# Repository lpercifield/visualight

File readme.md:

###**Visualight Hardware and Firmware**
Server code is available from this repo

####**Release Candidate GREEN**

Current Firmware Version: 1.1 (RC GREEN) library
More information: [Visualight.org][1]

* Arduino Library can be found in Firmware > Visualight
* Wiki can be found [here][2]

------
	
####Features:
* Show color (version) of firmware when you do a reset
* Ability to enable/disable WiFly LEDs from Arduino (top-level)
* Special character support in SSIDs (now supports &^%$#()!@ in network name)

####Fixes:
* Easier to reset WiFi with button (processButton() added to reconnect loops
* Debug toggling from Arduino?

[1]:http://visualight.org
[2]:https://github.com/lpercifield/visualight/wiki
[3]:https://github.com/lpercifield/Visualight_Server

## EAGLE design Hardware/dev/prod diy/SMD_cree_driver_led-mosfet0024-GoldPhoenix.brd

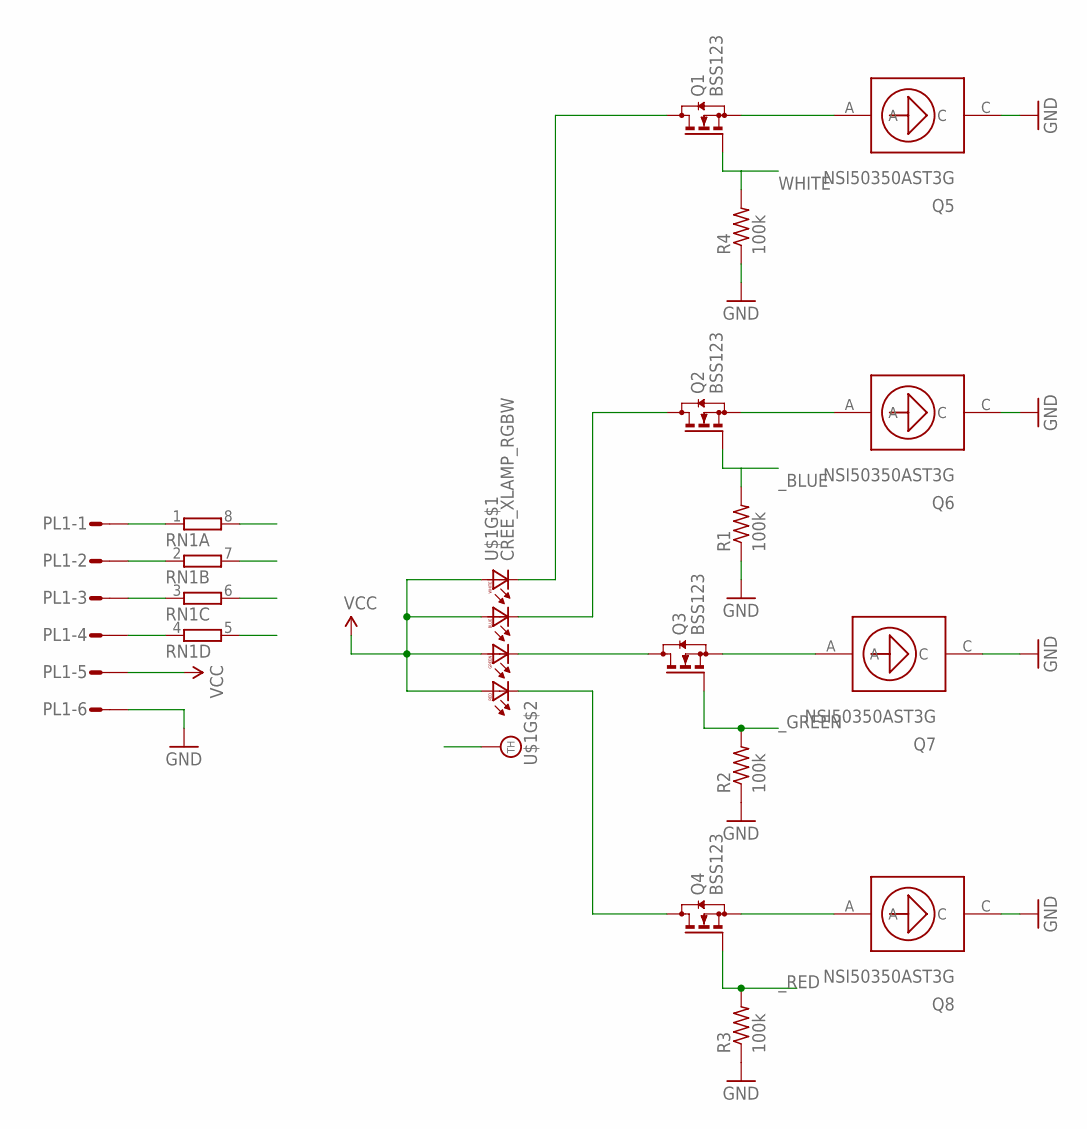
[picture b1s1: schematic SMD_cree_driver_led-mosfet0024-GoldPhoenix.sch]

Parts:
PL1: DF3-06R; DF3R-06
Q1, Q2, Q3, Q4: BSS123; SOT23
Q5, Q6, Q7, Q8: NSI50350AST3G; SMC-2
R1, R2, R3, R4: 100k; R0402
RN1: 4R-N0603-ARC; 0603-ARC
U$1: CREE_XLAMP_RGBW; CREE_XLAMP_XML

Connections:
BLUE_DRIVER: Q2.3 (D), U$1.6 (BC)
BLUE_PWM_IN: PL1.3, RN1.3 (1)
GND: PL1.6, Q5.C, Q6.C, Q7.C, Q8.C, R1.1, R2.1, R3.1, R4.1
GREEN_DRIVER: Q3.3 (D), U$1.7 (GC)
GREEN_PWM_IN: PL1.4, RN1.4 (1)
unnamed: Q2.2 (S), Q6.A
unnamed: Q4.2 (S), Q8.A
unnamed: Q3.2 (S), Q7.A
unnamed: Q1.2 (S), Q5.A
RED_DRIVER: Q4.3 (D), U$1.8 (RC)
RED_PWM_IN: PL1.2, RN1.2 (1)
THERM: U$1.P$1 (TH)
VCC: PL1.5, U$1.1 (RA), U$1.2 (GA), U$1.3 (BA), U$1.4 (WA)
WHITE: Q1.1 (G), R4.2, RN1.8 (2)
WHITE_DRIVER: Q1.3 (D), U$1.5 (WC)
WHITE_PWM_IN: PL1.1, RN1.1
_BLUE: Q2.1 (G), R1.2, RN1.6 (2)
_GREEN: Q3.1 (G), R2.2, RN1.5 (2)
_RED: Q4.1 (G), R3.2, RN1.7 (2)

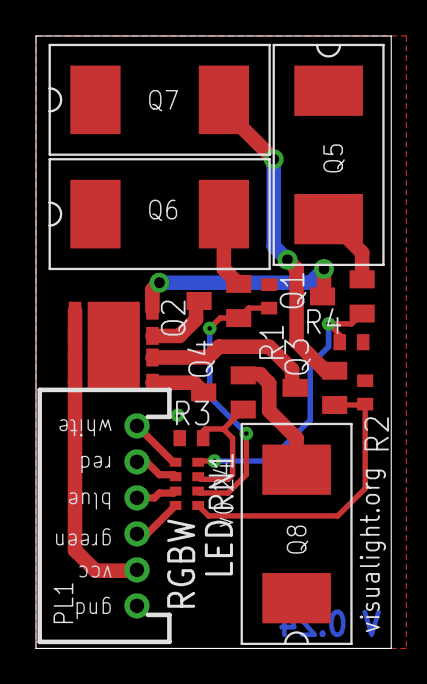
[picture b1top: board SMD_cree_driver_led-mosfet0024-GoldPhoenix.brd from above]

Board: 2 copper layers, 19.7 x 34.0 mm, 15 parts (0 on the bottom side), 18 nets.

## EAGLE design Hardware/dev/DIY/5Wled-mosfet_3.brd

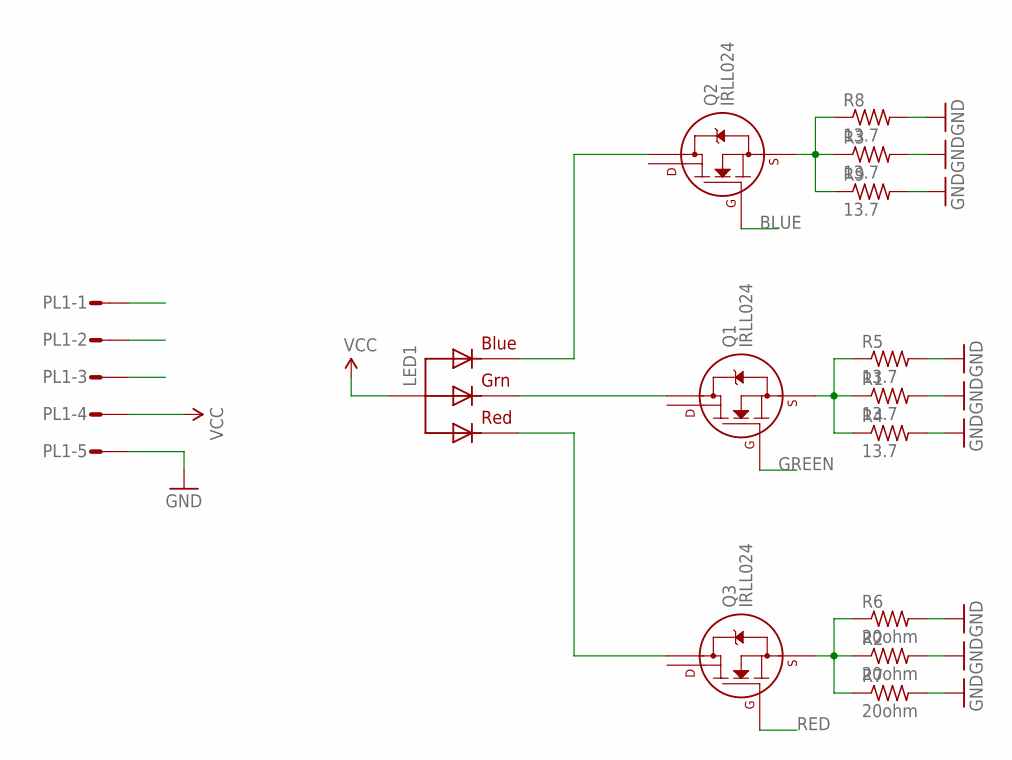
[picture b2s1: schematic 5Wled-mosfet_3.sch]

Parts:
LED1: RGBLED_CA4.5MM; 5WRGBLED
PL1: DF3-05R; DF3R-05
Q1, Q2, Q3: IRLL024; SOT-223
R1, R3, R4, R5, R8, R9: 13.7; R1210
R2, R6, R7: 20ohm; R1210

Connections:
BLUE: PL1.3, Q2.1 (G)
GND: PL1.5, R1.2, R2.2, R3.2, R4.2, R5.2, R6.2, R7.2, R8.2, R9.2
GREEN: PL1.1, Q1.1 (G)
unnamed: LED1.3 (GREEN), Q1.2 (D1)
unnamed: LED1.1 (BLUE), Q2.2 (D1)
unnamed: LED1.2 (RED), Q3.2 (D1)
unnamed: Q1.3 (S), R1.1, R4.1, R5.1
unnamed: Q3.3 (S), R2.1, R6.1, R7.1
unnamed: Q2.3 (S), R3.1, R8.1, R9.1
RED: PL1.2, Q3.1 (G)
VCC: LED1.4 (VCC), PL1.4

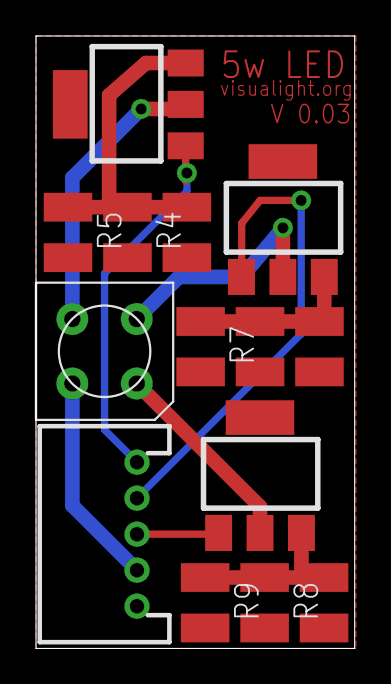
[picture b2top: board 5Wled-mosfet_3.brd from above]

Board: 2 copper layers, 17.7 x 34.0 mm, 14 parts (0 on the bottom side), 11 nets.

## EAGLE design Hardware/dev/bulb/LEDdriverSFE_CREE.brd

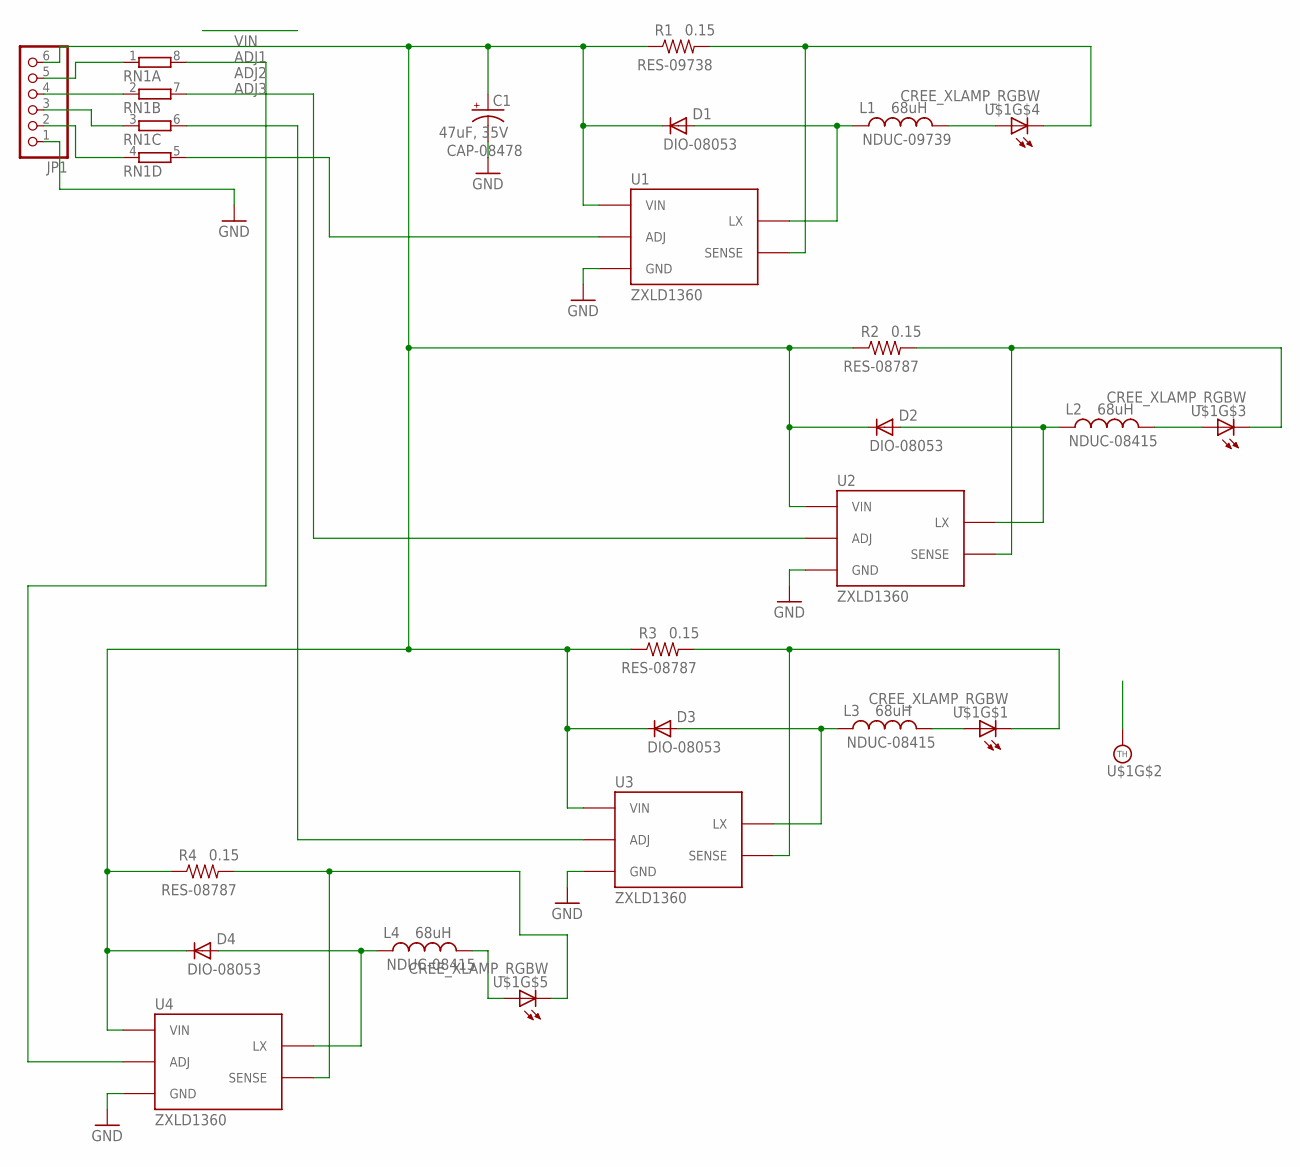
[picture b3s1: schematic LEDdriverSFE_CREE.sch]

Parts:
C1: 47uF, 35V; PANASONIC_D
D1, D2, D3, D4: MBRA140; SMA-DIODE
JP1: PINHD-1X6; 1X06
L1, L2, L3, L4: 68uH; CR75
R1, R2, R3, R4: 0.15; 0603-RES
RN1: 4R-NEXBV8V; EXBV8V
U1, U2, U3, U4: ZXLD1360; SOT23-5
U$1: CREE_XLAMP_RGBW; CREE_XLAMP_XML

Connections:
ADJ1: RN1.5 (2), U1.3 (ADJ)
ADJ2: RN1.7 (2), U2.3 (ADJ)
ADJ3: RN1.6 (2), U3.3 (ADJ)
GND: C1.-, JP1.1, U1.2 (GND), U2.2 (GND), U3.2 (GND), U4.2 (GND)
unnamed: L1.P$2 (2), U$1.3 (A)
unnamed: D2.A, L2.P$1 (1), U2.1 (LX)
unnamed: R2.2, U2.4 (SENSE), U$1.7 (C)
unnamed: D1.A, L1.P$1 (1), U1.1 (LX)
unnamed: R1.2, U1.4 (SENSE), U$1.6 (C)
unnamed: L2.P$2 (2), U$1.2 (A)
unnamed: D3.A, L3.P$1 (1), U3.1 (LX)
unnamed: R3.2, U3.4 (SENSE), U$1.8 (C)
unnamed: L3.P$2 (2), U$1.1 (A)
unnamed: D4.A, L4.P$1 (1), U4.1 (LX)
unnamed: R4.2, U4.4 (SENSE), U$1.5 (C)
unnamed: RN1.8 (2), U4.3 (ADJ)
unnamed: JP1.2, RN1.4 (1)
unnamed: JP1.5, RN1.1
unnamed: L4.P$2 (2), U$1.4 (A)
unnamed: JP1.4, RN1.2 (1)
unnamed: JP1.3, RN1.3 (1)
THERM: U$1.P$1 (TH)
VIN: C1.+, D1.C, D2.C, D3.C, D4.C, JP1.6, R1.1, R2.1, R3.1, R4.1, U1.5 (VIN), U2.5 (VIN), U3.5 (VIN), U4.5 (VIN)

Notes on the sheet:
NDUC-09739
RES-09738
CAP-08478
DIO-08053
NDUC-08415
RES-08787

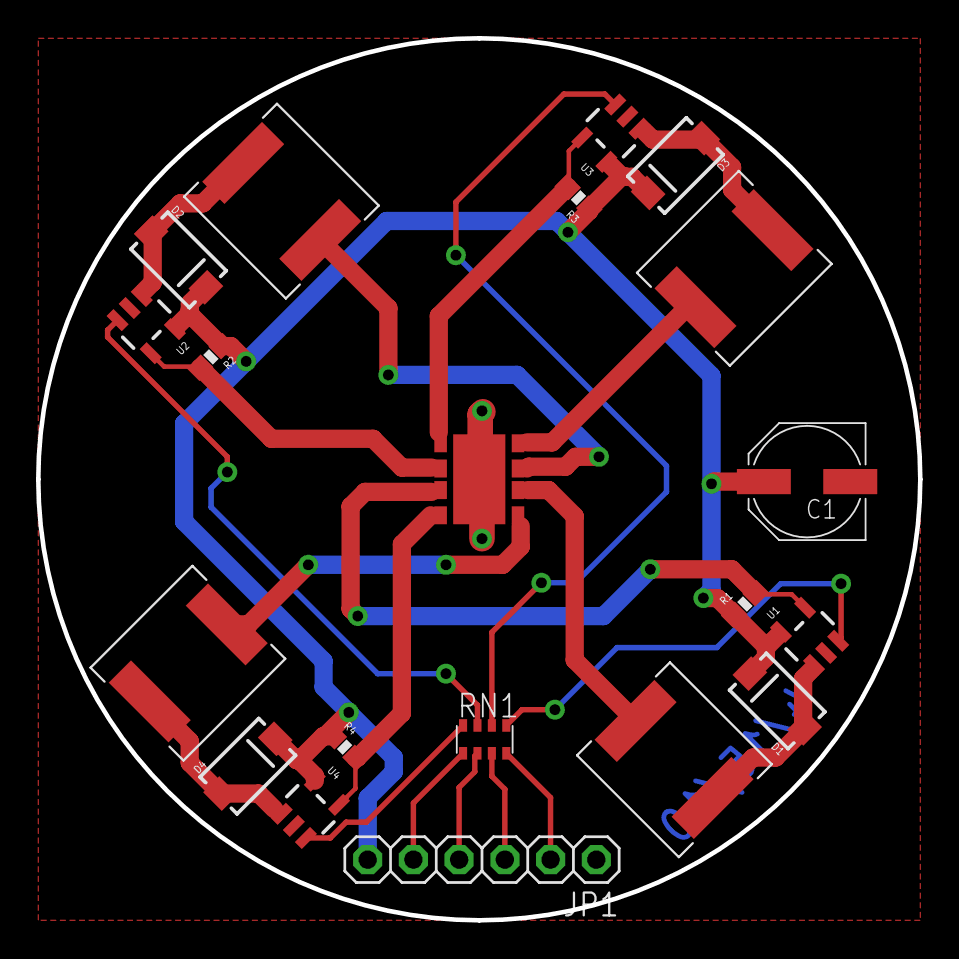
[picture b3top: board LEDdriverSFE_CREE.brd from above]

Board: 2 copper layers, 49.0 x 49.0 mm, 20 parts (0 on the bottom side), 22 nets.

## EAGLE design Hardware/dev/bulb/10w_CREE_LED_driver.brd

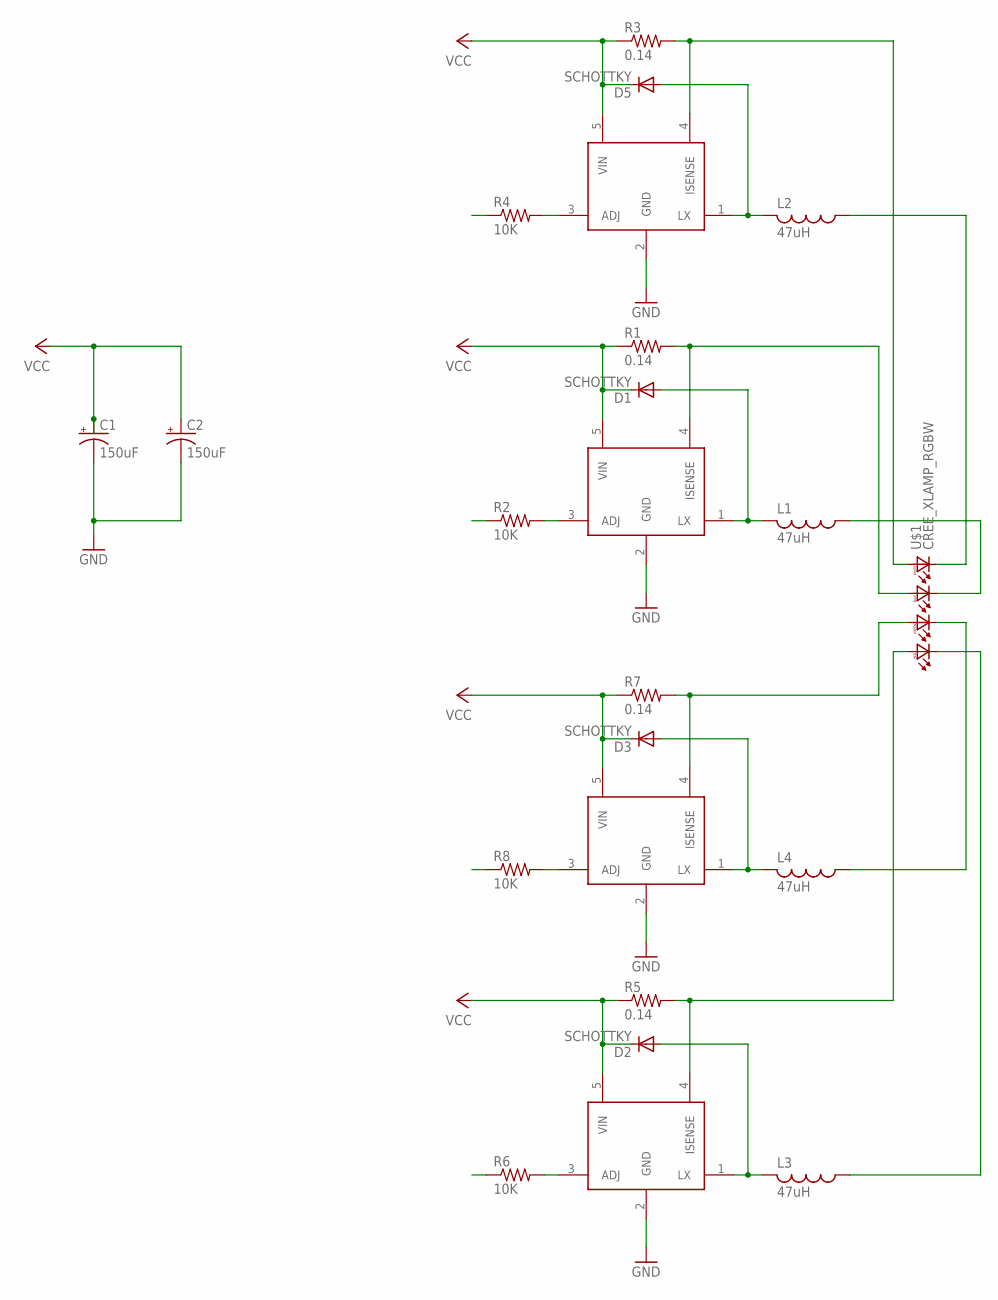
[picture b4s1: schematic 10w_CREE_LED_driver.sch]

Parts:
C1, C2: 150uF; 175TMP-0810
D1, D2, D3, D5: SCHOTTKY; DO214AC
L1, L2, L3, L4: 47uH; TDK6045
R1, R3, R5, R7: 0.14; R0805
R2, R4, R6, R8: 10K; R0603
U$1: CREE_XLAMP_RGBW; CREE_XLAMP_XML
U$2, U$3, U$4, U$6: ZLED7000-LEDDRIVER; SOT89-5

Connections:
GND: C1.-, C2.-, U$2.2 (GND), U$3.2 (GND), U$4.2 (GND), U$6.2 (GND)
unnamed: R2.2, U$2.3 (ADJ)
unnamed: R1.2, U$1.3 (BA), U$2.4 (ISENSE)
unnamed: L2.1, U$1.5 (WC)
unnamed: D1.A, L1.2, U$2.1 (LX)
unnamed: R3.2, U$1.4 (WA), U$6.4 (ISENSE)
unnamed: D5.A, L2.2, U$6.1 (LX)
unnamed: R4.2, U$6.3 (ADJ)
unnamed: R5.2, U$1.1 (RA), U$3.4 (ISENSE)
unnamed: D2.A, L3.2, U$3.1 (LX)
unnamed: R6.2, U$3.3 (ADJ)
unnamed: R7.2, U$1.2 (GA), U$4.4 (ISENSE)
unnamed: D3.A, L4.2, U$4.1 (LX)
unnamed: R8.2, U$4.3 (ADJ)
unnamed: L1.1, U$1.6 (BC)
unnamed: L4.1, U$1.7 (GC)
unnamed: L3.1, U$1.8 (RC)
VCC: C1.+, C2.+, D1.C, D2.C, D3.C, D5.C, R1.1, R3.1, R5.1, R7.1, U$2.5 (VIN), U$3.5 (VIN), U$4.5 (VIN), U$6.5 (VIN)

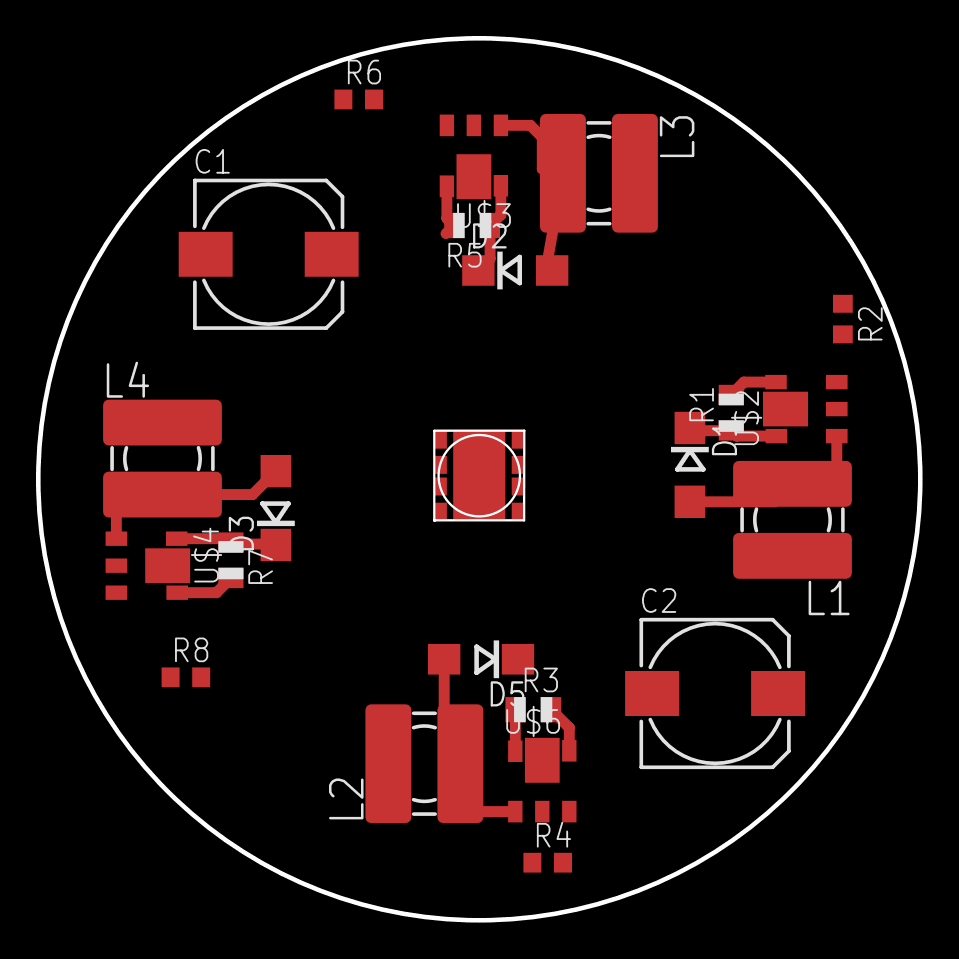
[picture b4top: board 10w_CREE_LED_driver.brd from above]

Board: 2 copper layers, 49.0 x 49.0 mm, 23 parts (0 on the bottom side), 18 nets.

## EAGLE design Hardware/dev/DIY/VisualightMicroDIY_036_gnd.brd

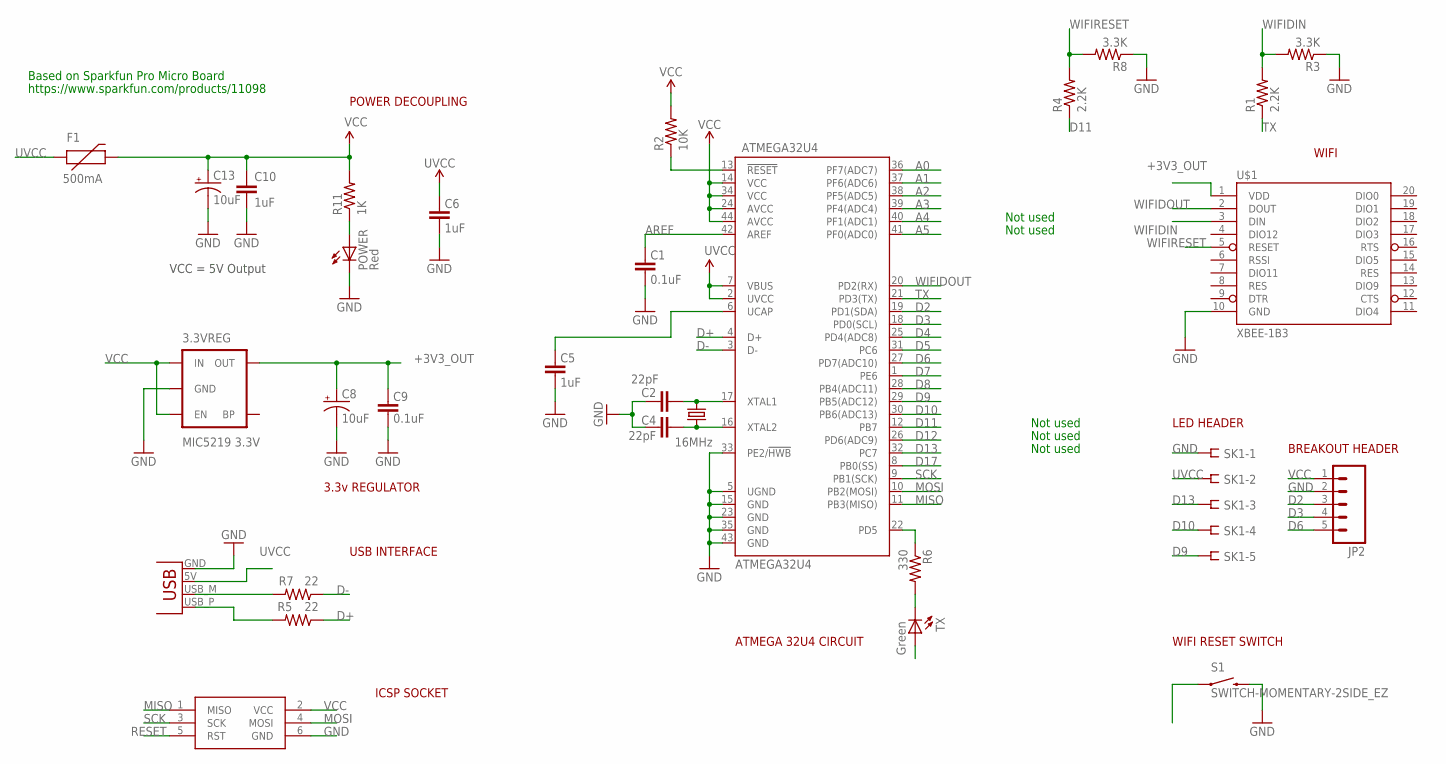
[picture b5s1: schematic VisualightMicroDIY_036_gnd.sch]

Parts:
3.3VREG: MIC5219 3.3V; SOT23-5
ATMEGA32U4: ATMEGA32U4; SPARKFUN-DIGITALIC_TQFP44
C1, C9: 0.1uF; 0402-CAP
C2, C4: 22pF; 0402-CAP
C5, C6, C10: 1uF; 0402-CAP
C8, C13: 10uF; EIA3216
F1: 500mA; PTC-1206
ISP1: AVRISP-6; AVRISP
JP2: M05PTH; 1X05
POWER: Red; LED-0603
R1, R4: 2.2K; 0402-RES
R2: 10K; 0402-RES
R3, R8: 3.3K; 0402-RES
R5, R7: 22; 0402-RES
R6: 330; 0402-RES
R11: 1K; 0402-RES
S1: SWITCH-MOMENTARY-2SIDE_EZ; TACTILE-PTH-SIDEEZ
SK1: DF3-05S; DF3S-05
TX: Green; LED-0603
U$1: XBEE-1B3; XBEE-SMD
X2: USBPCB; USB-A-PCB
Y1: 16MHz; CRYSTAL-SMD-5X3

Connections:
+3V3_OUT: 3.3VREG.5 (OUT), C8.A (+), C9.2, U$1.1 (VDD)
A0: ATMEGA32U4.36 (PF7(ADC7))
A1: ATMEGA32U4.37 (PF6(ADC6))
A2: ATMEGA32U4.38 (PF5(ADC5))
A3: ATMEGA32U4.39 (PF4(ADC4))
A4: ATMEGA32U4.40 (PF1(ADC1))
A5: ATMEGA32U4.41 (PF0(ADC0))
AREF: ATMEGA32U4.42 (AREF), C1.2
D2: ATMEGA32U4.19 (PD1(SDA)), JP2.3
D3: ATMEGA32U4.18 (PD0(SCL)), JP2.4
D4: ATMEGA32U4.25 (PD4(ADC8))
D5: ATMEGA32U4.31 (PC6)
D6: ATMEGA32U4.27 (PD7(ADC10)), JP2.5
D7: ATMEGA32U4.1 (PE6), S1.1
D8: ATMEGA32U4.28 (PB4(ADC11))
D9: ATMEGA32U4.29 (PB5(ADC12)), SK1.5
D10: ATMEGA32U4.30 (PB6(ADC13)), SK1.4
D11: ATMEGA32U4.12 (PB7), R4.1
D12: ATMEGA32U4.26 (PD6(ADC9))
D13: ATMEGA32U4.32 (PC7), SK1.3
D17: ATMEGA32U4.8 (PB0(SS))
D+: ATMEGA32U4.4 (D+), R5.1
D-: ATMEGA32U4.3 (D-), R7.1
GND: 3.3VREG.2 (GND), ATMEGA32U4.5 (UGND), ATMEGA32U4.15 (GND), ATMEGA32U4.23 (GND), ATMEGA32U4.33 (PE2/!HWB), ATMEGA32U4.35 (GND), ATMEGA32U4.43 (GND), C1.1, C2.2, C4.2, C5.1, C6.1, C8.C (-), C9.1, C10.2, C13.C (-), ISP1.6 (GND), JP2.2, POWER.C, R3.1, R8.1, S1.2, SK1.1, U$1.10 (GND), X2.GND
MISO: ATMEGA32U4.11 (PB3(MISO)), ISP1.1 (MISO)
MOSI: ATMEGA32U4.10 (PB2(MOSI)), ISP1.4 (MOSI)
unnamed: ATMEGA32U4.16 (XTAL2), C4.1, Y1.1
unnamed: ATMEGA32U4.17 (XTAL1), C2.1, Y1.3 (2)
unnamed: ATMEGA32U4.6 (UCAP), C5.2
unnamed: R7.2, X2.USB_M (D-)
unnamed: R6.2, TX.C
unnamed: R5.2, X2.USB_P (D+)
unnamed: POWER.A, R11.1
RESET: ATMEGA32U4.13 (!RESET), ISP1.5 (RST), R2.1
SCK: ATMEGA32U4.9 (PB1(SCK)), ISP1.3 (SCK)
TX: ATMEGA32U4.21 (PD3(TX)), R1.1
TXLED: ATMEGA32U4.22 (PD5), R6.1
UVCC: ATMEGA32U4.2 (UVCC), ATMEGA32U4.7 (VBUS), C6.2, F1.1, SK1.2, X2.5V (VBUS)
VCC: 3.3VREG.1 (IN), 3.3VREG.3 (EN), ATMEGA32U4.14 (VCC), ATMEGA32U4.24 (AVCC), ATMEGA32U4.34 (VCC), ATMEGA32U4.44 (AVCC), C10.1, C13.A (+), F1.2, ISP1.2 (VCC), JP2.1, R2.2, R11.2, TX.A
WIFIDIN: R1.2, R3.2, U$1.3 (DIN)
WIFIDOUT: ATMEGA32U4.20 (PD2(RX)), U$1.2 (DOUT)
WIFIRESET: R4.2, R8.2, U$1.5 (RESET)

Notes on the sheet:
VCC = 5V Output
Not used
Based on Sparkfun Pro Micro Board
https://www.sparkfun.com/products/11098
USB INTERFACE
ICSP SOCKET
3.3v REGULATOR
POWER DECOUPLING
ATMEGA 32U4 CIRCUIT
WIFI RESET SWITCH
BREAKOUT HEADER
WIFI
LED HEADER

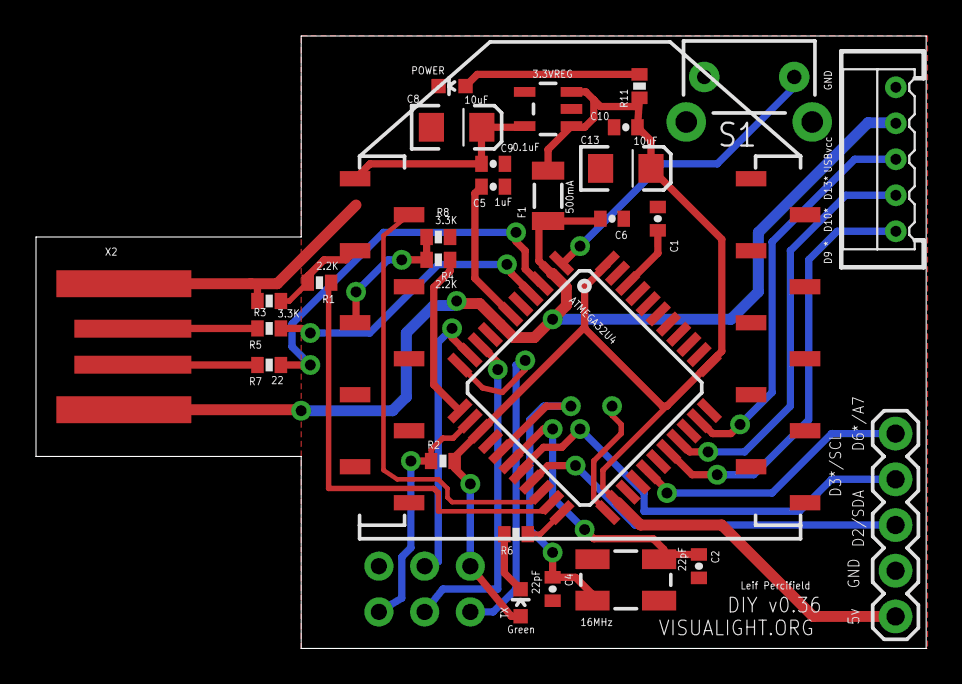
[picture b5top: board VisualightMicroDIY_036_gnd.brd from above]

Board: 2 copper layers, 49.5 x 34.0 mm, 30 parts (1 on the bottom side), 31 nets.

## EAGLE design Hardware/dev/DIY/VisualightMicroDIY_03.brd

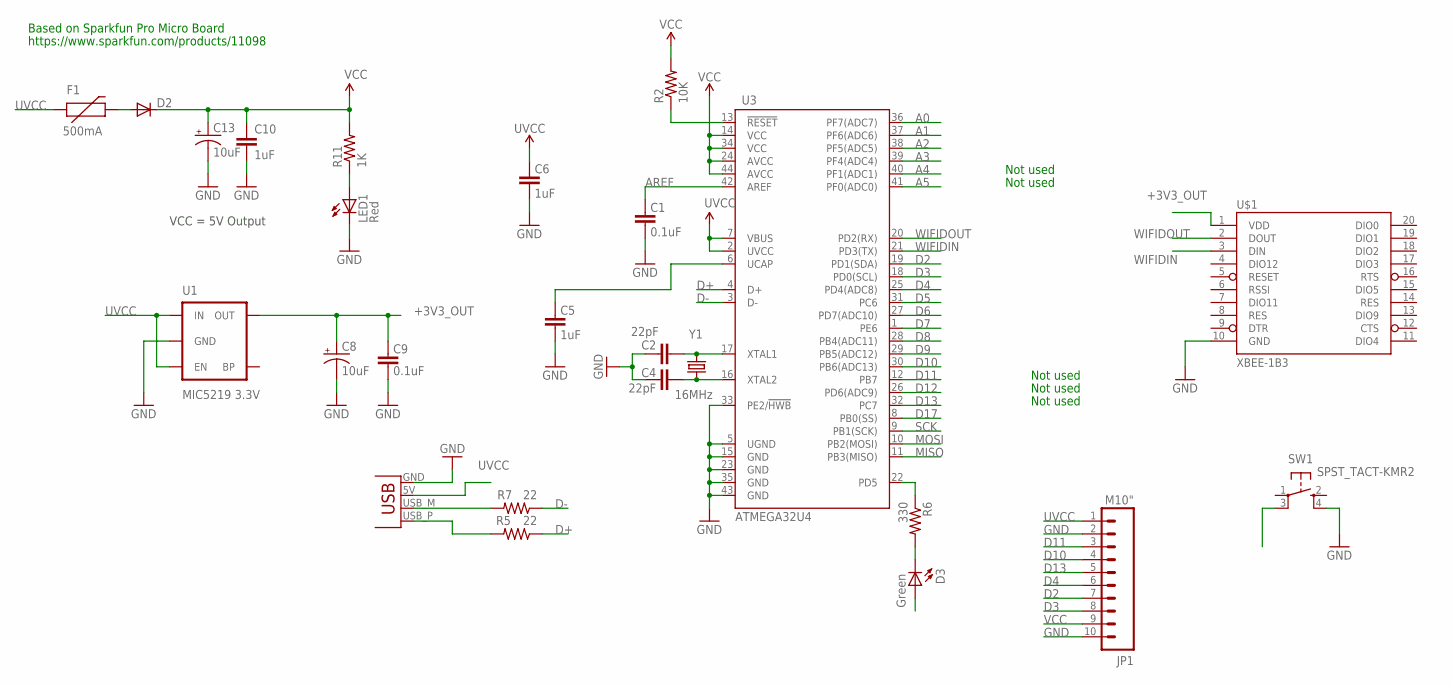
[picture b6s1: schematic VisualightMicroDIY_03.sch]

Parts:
C1, C9: 0.1uF; 0402-CAP
C2, C4: 22pF; 0402-CAP
C5, C6, C10: 1uF; 0402-CAP
C8, C13: 10uF; EIA3216
D2: DIODESOD; SOD-323
D3: Green; LED-0603
F1: 500mA; PTC-1206
JP1: M10"; 1X10
LED1: Red; LED-0603
R2: 10K; 0402-RES
R5, R7: 22; 0402-RES
R6: 330; 0402-RES
R11: 1K; 0402-RES
SW1: SPST_TACT-KMR2; KMR2
U1: MIC5219 3.3V; SOT23-5
U3: ATMEGA32U4; SPARKFUN-DIGITALIC_TQFP44
U$1: XBEE-1B3; XBEE-SMD
X2: USBPCB; USB-A-PCB
Y1: 16MHz; CRYSTAL-SMD-5X3

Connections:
+3V3_OUT: C8.A (+), C9.2, U1.5 (OUT), U$1.1 (VDD)
A0: U3.36 (PF7(ADC7))
A1: U3.37 (PF6(ADC6))
A2: U3.38 (PF5(ADC5))
A3: U3.39 (PF4(ADC4))
A4: U3.40 (PF1(ADC1))
A5: U3.41 (PF0(ADC0))
AREF: C1.2, U3.42 (AREF)
D2: JP1.7, U3.19 (PD1(SDA))
D3: JP1.8, U3.18 (PD0(SCL))
D4: JP1.6, U3.25 (PD4(ADC8))
D5: U3.31 (PC6)
D6: U3.27 (PD7(ADC10))
D7: SW1.3 (P1), U3.1 (PE6)
D8: U3.28 (PB4(ADC11))
D9: U3.29 (PB5(ADC12))
D10: JP1.4, U3.30 (PB6(ADC13))
D11: JP1.3, U3.12 (PB7)
D12: U3.26 (PD6(ADC9))
D13: JP1.5, U3.32 (PC7)
D17: U3.8 (PB0(SS))
D+: R5.1, U3.4 (D+)
D-: R7.1, U3.3 (D-)
GND: C1.1, C2.2, C4.2, C5.1, C6.1, C8.C (-), C9.1, C10.2, C13.C (-), JP1.2, JP1.10, LED1.C, SW1.4 (S1), U1.2 (GND), U3.5 (UGND), U3.15 (GND), U3.23 (GND), U3.33 (PE2/!HWB), U3.35 (GND), U3.43 (GND), U$1.10 (GND), X2.GND
MISO: U3.11 (PB3(MISO))
MOSI: U3.10 (PB2(MOSI))
unnamed: C4.1, U3.16 (XTAL2), Y1.1
unnamed: C2.1, U3.17 (XTAL1), Y1.3 (2)
unnamed: C5.2, U3.6 (UCAP)
unnamed: R7.2, X2.USB_M (D-)
unnamed: D3.C, R6.2
unnamed: R5.2, X2.USB_P (D+)
unnamed: D2.2 (A), F1.2
unnamed: LED1.A, R11.1
RESET: R2.1, U3.13 (!RESET)
SCK: U3.9 (PB1(SCK))
TXLED: R6.1, U3.22 (PD5)
UVCC: C6.2, D3.A, F1.1, JP1.1, U1.1 (IN), U1.3 (EN), U3.2 (UVCC), U3.7 (VBUS), X2.5V (VBUS)
VCC: C10.1, C13.A (+), D2.1 (C), JP1.9, R2.2, R11.2, U3.14 (VCC), U3.24 (AVCC), U3.34 (VCC), U3.44 (AVCC)
WIFIDIN: U3.21 (PD3(TX)), U$1.3 (DIN)
WIFIDOUT: U3.20 (PD2(RX)), U$1.2 (DOUT)

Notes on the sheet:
VCC = 5V Output
Not used
Based on Sparkfun Pro Micro Board
https://www.sparkfun.com/products/11098

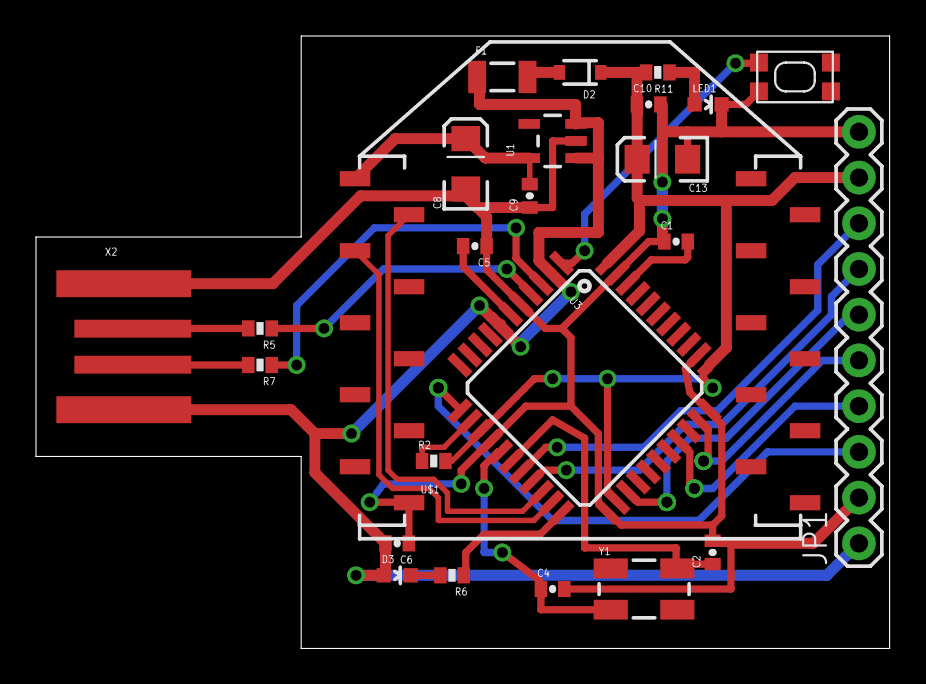
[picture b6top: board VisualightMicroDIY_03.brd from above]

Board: 2 copper layers, 47.4 x 34.0 mm, 25 parts (0 on the bottom side), 26 nets.

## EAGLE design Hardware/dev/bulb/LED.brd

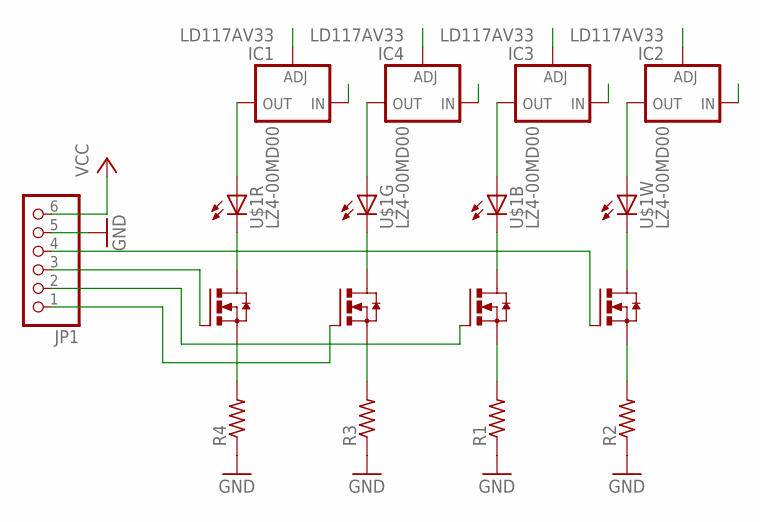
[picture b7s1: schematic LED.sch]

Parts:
IC1, IC2, IC3, IC4: LD117AV33; TO220L1
JP1: PINHD-1X6; 1X06
Q1, Q2, Q3, Q4: N-HEXFET_SOT323-; SOT223
R1, R2, R3, R4: R-US_0204/7; 0204/7
U$1: LZ4-00MD00; LZ4-00MD0

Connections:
BLUE: JP1.2, Q1.1 (G)
GND: IC1.1 (ADJ), IC2.1 (ADJ), IC3.1 (ADJ), IC4.1 (ADJ), JP1.5, R1.1, R2.1, R3.1, R4.1
GREEN: JP1.1, Q2.1 (G)
unnamed: Q2.3 (S), R3.2
unnamed: Q3.3 (S), R4.2
unnamed: Q1.3 (S), R1.2
unnamed: Q4.3 (S), R2.2
unnamed: Q3.4 (D), U$1.4 (C)
unnamed: Q2.4 (D), U$1.6 (C)
unnamed: Q1.4 (D), U$1.8 (C)
unnamed: Q4.4 (D), U$1.2 (C)
unnamed: IC2.2 (OUT), U$1.1 (A)
unnamed: IC3.2 (OUT), U$1.7 (A)
unnamed: IC4.2 (OUT), U$1.5 (A)
unnamed: IC1.2 (OUT), U$1.3 (A)
RED: JP1.3, Q3.1 (G)
VCC: IC1.3 (IN), IC2.3 (IN), IC3.3 (IN), IC4.3 (IN), JP1.6
WHITE: JP1.4, Q4.1 (G)

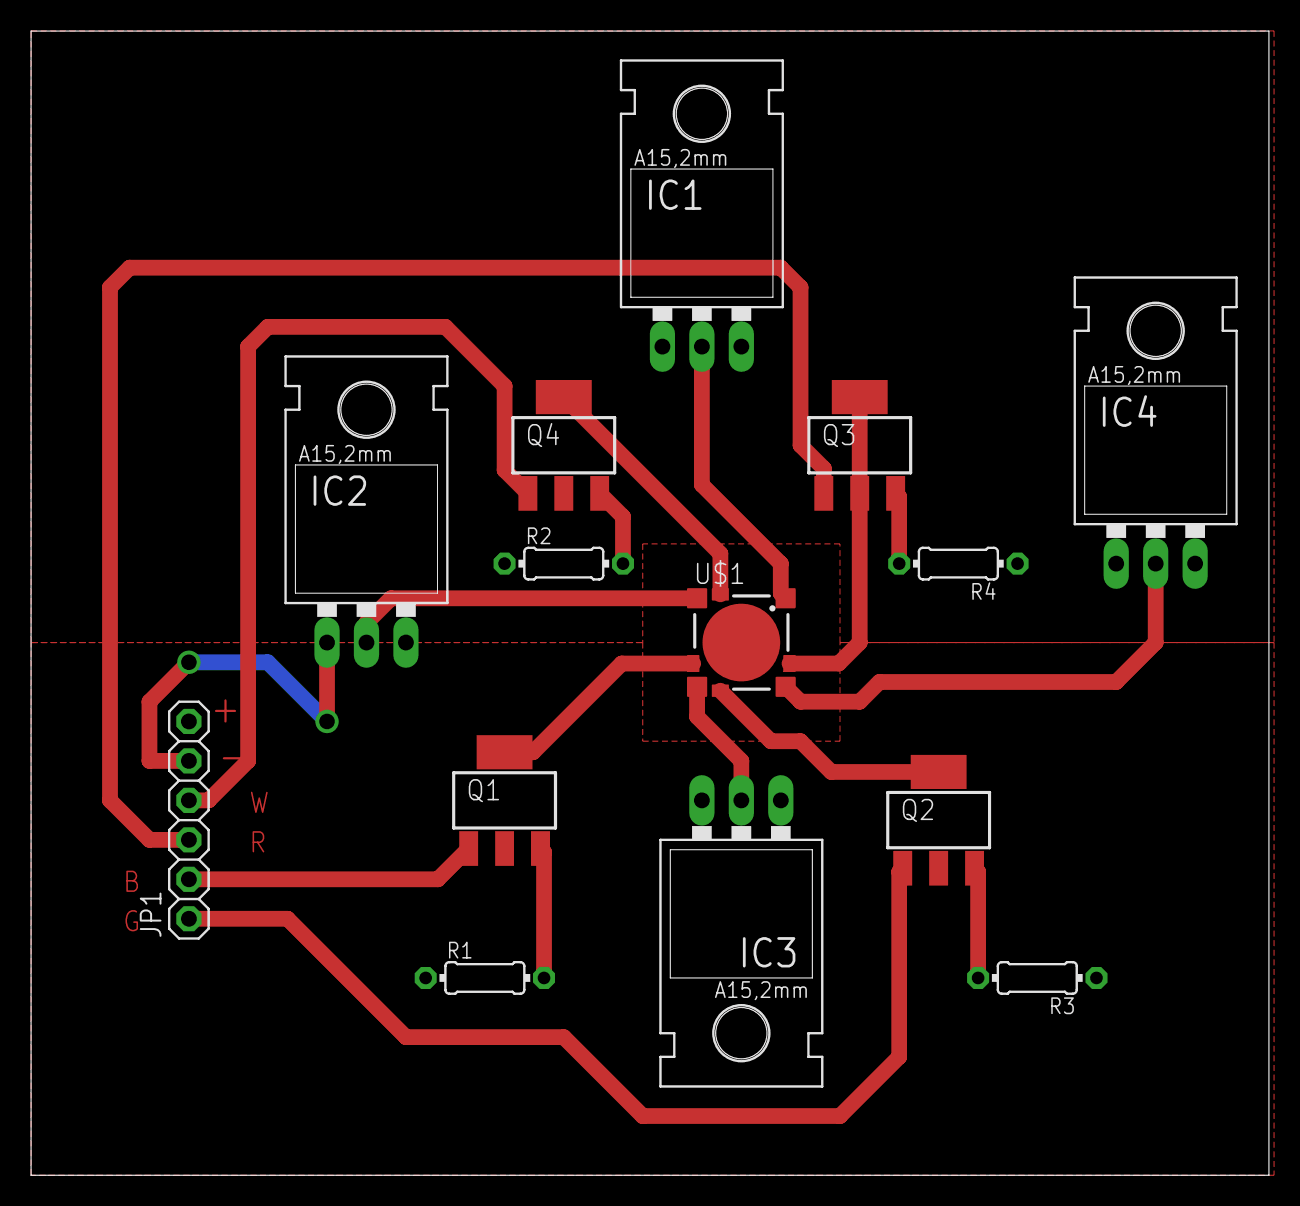
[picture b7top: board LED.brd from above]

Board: 2 copper layers, 79.7 x 73.7 mm, 14 parts (0 on the bottom side), 18 nets.

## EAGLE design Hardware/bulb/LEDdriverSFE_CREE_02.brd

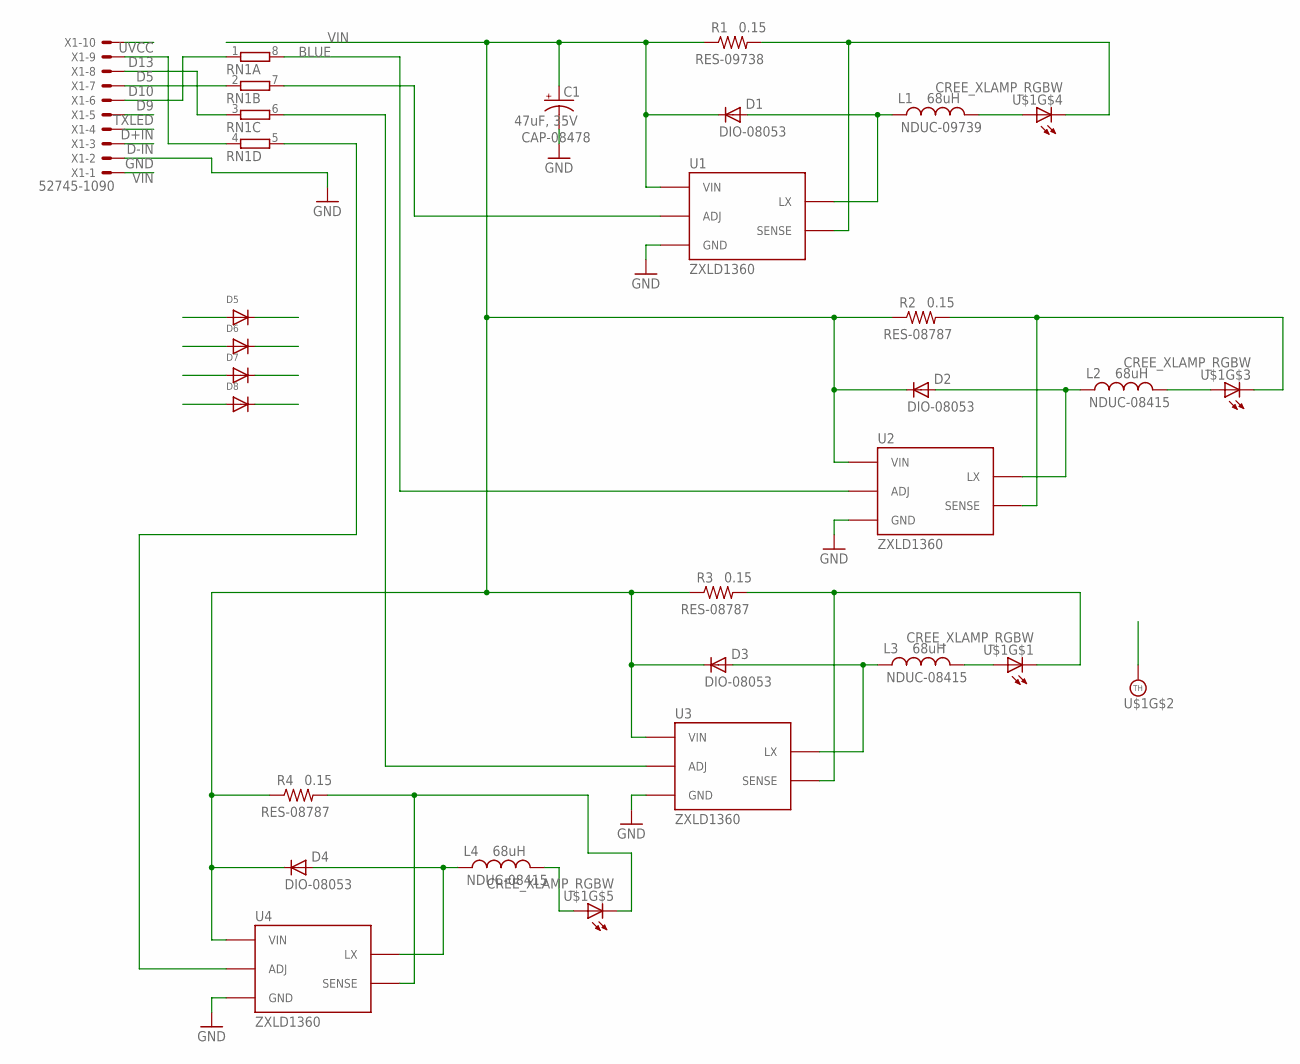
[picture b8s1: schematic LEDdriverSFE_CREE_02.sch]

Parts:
C1: 47uF, 35V; PANASONIC_D
D1, D2, D3, D4: MBRA140; SMA-DIODE
D5, D6, D7, D8: DIODESOD-323F; SOD-323F
L1, L2, L3, L4: 68uH; TDK6045
R1, R2, R3, R4: 0.15; 0603-RES
RN1: 4R-NEXBV8V; EXBV8V
U1, U2, U3, U4: ZXLD1360; SOT23-5
U$1: CREE_XLAMP_RGBW; CREE_XLAMP_XML
X1: 52745-1090

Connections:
BLUE: RN1.8 (2), U2.3 (ADJ)
D5: D8.C, RN1.3 (1), X1.8
D9: D5.C, RN1.1, X1.6
D10: D6.C, RN1.2 (1), X1.7
D13: D7.C, RN1.4 (1), X1.9
D+IN: X1.4
D-IN: X1.3
GND: C1.-, D5.A, D6.A, D7.A, D8.A, U1.2 (GND), U2.2 (GND), U3.2 (GND), U4.2 (GND), X1.2
GREEN: RN1.7 (2), U1.3 (ADJ)
unnamed: L1.2, U$1.3 (A)
unnamed: D2.A, L2.1, U2.1 (LX)
unnamed: R2.2, U2.4 (SENSE), U$1.7 (C)
unnamed: D1.A, L1.1, U1.1 (LX)
unnamed: R1.2, U1.4 (SENSE), U$1.6 (C)
unnamed: L2.2, U$1.2 (A)
unnamed: D3.A, L3.1, U3.1 (LX)
unnamed: R3.2, U3.4 (SENSE), U$1.8 (C)
unnamed: L3.2, U$1.1 (A)
unnamed: D4.A, L4.1, U4.1 (LX)
unnamed: R4.2, U4.4 (SENSE), U$1.5 (C)
unnamed: L4.2, U$1.4 (A)
RED: RN1.5 (2), U4.3 (ADJ)
THERM: U$1.P$1 (TH)
TXLED: X1.5
UVCC: X1.10
VIN: C1.+, D1.C, D2.C, D3.C, D4.C, R1.1, R2.1, R3.1, R4.1, U1.5 (VIN), U2.5 (VIN), U3.5 (VIN), U4.5 (VIN), X1.1
WHITE: RN1.6 (2), U3.3 (ADJ)

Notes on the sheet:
NDUC-09739
RES-09738
CAP-08478
DIO-08053
NDUC-08415
RES-08787

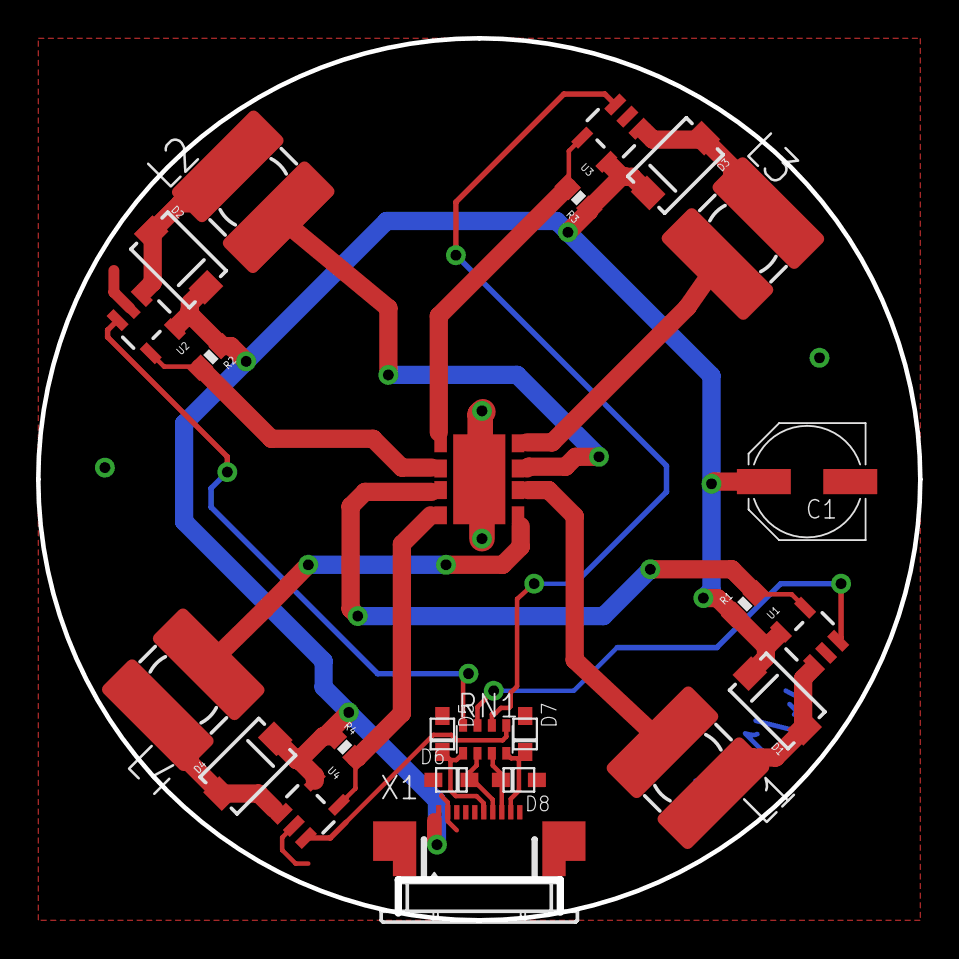
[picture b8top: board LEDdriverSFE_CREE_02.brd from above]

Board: 2 copper layers, 48.8 x 48.8 mm, 24 parts (0 on the bottom side), 22 nets.

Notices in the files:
parts and their libraries:
SparkFun-Aesthetics: Licensing: CC v3.0 Share-Alike You are welcome to use this library for commercial purposes.
